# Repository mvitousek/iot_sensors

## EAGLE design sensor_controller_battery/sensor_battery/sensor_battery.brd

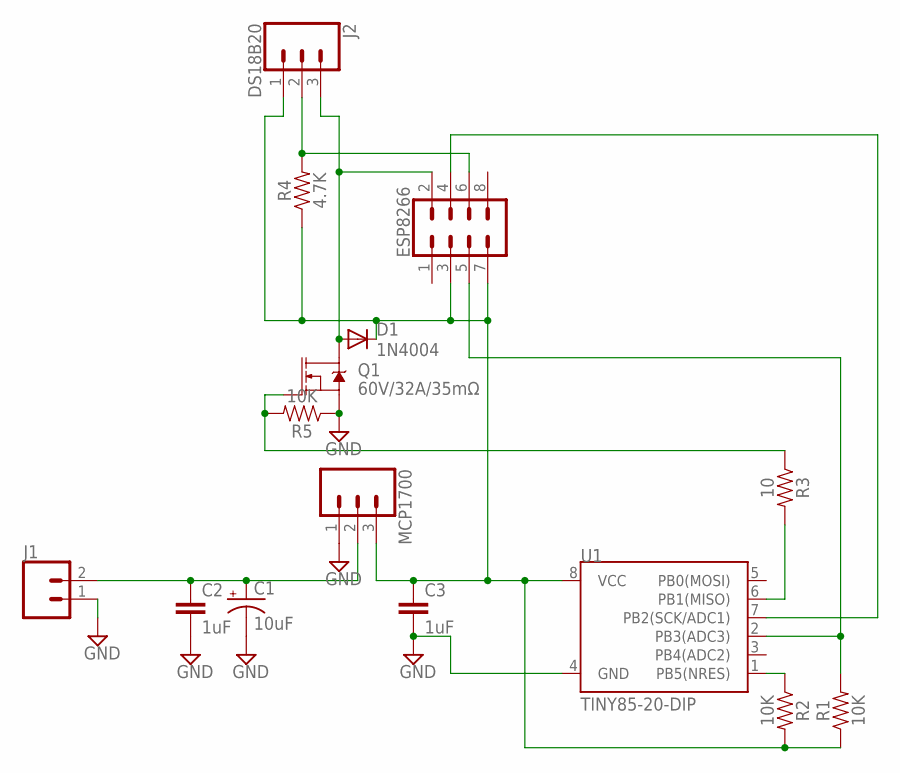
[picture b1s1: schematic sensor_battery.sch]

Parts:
C1: 10uF; CPOL-RADIAL-2.5MM-5MM
C2, C3: 1uF; C5B2.5
D1: 1N4004; DO41-10
ESP8266: CONN_04X2; 2X4
J1: CONN_02-JST-2-PTH-NO_SILK; JST-2-PTH-NS
J2: DS18B20; JST-3-PTH
MCP1700: CONN_03; 1X03
Q1: 60V/32A/35mΩ; TO220V
R1, R2, R5: 10K; AXIAL-0.3
R3: 10; AXIAL-0.3
R4: 4.7K; AXIAL-0.3
U1: TINY85-20-DIP; DIP08_MCU

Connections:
3.3V: C3.1, D1.C, ESP8266.3, ESP8266.7, J2.1, MCP1700.3, R1.P$1 (1), R2.P$2 (2), R4.P$1 (1), U1.8 (VCC)
5V: C1.1 (+), C2.1, J1.2, MCP1700.2
ARST: R2.P$1 (1), U1.1 (PB5(NRES))
DSIG: ESP8266.4, U1.7 (PB2(SCK/ADC1))
ERST: ESP8266.5, R1.P$2 (2), U1.2 (PB3(ADC3))
FGND: D1.A, ESP8266.2, J2.3, Q1.2 (D)
FSIG: Q1.1 (G), R3.P$1 (1), R5.P$2 (2)
FSIGFIRST: R3.P$2 (2), U1.6 (PB1(MISO))
GND: C1.2 (-), C2.2, C3.2, J1.1, MCP1700.1, Q1.3 (S), R5.P$1 (1), U1.4 (GND)
TDAT: ESP8266.6, J2.2, R4.P$2 (2)

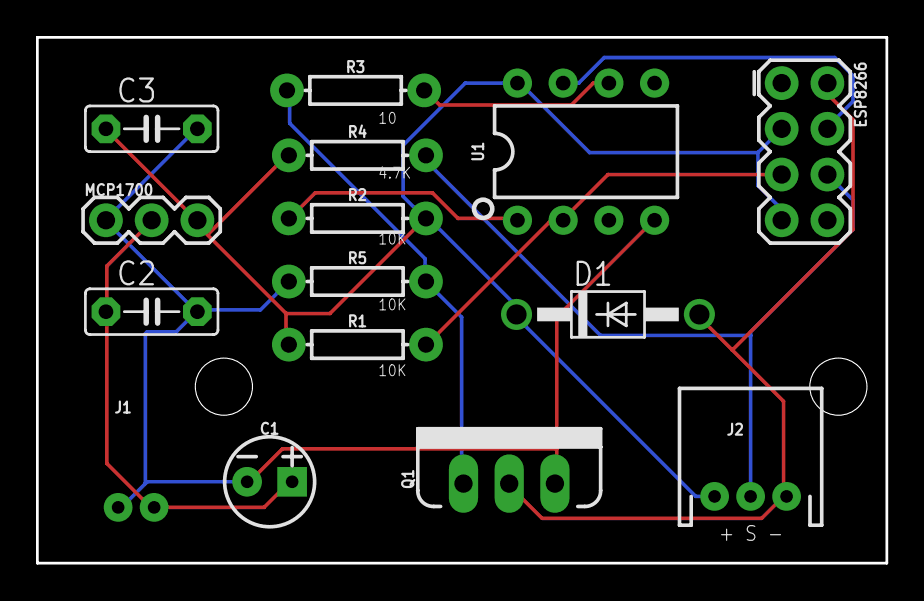
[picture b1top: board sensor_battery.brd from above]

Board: 2 copper layers, 47.2 x 29.2 mm, 15 parts (0 on the bottom side), 10 nets.

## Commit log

2018-02-17 initial
2018-02-19 Switching to using actual deep sleep on ATtiny
2018-02-19 board redesigns
2018-03-05 adding eagle files, updates

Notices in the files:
parts and their libraries:
SparkFun-Capacitors: Licensing: Creative Commons ShareAlike 4.0 International - https://creativecommons.org/licenses/by-sa/4.0
